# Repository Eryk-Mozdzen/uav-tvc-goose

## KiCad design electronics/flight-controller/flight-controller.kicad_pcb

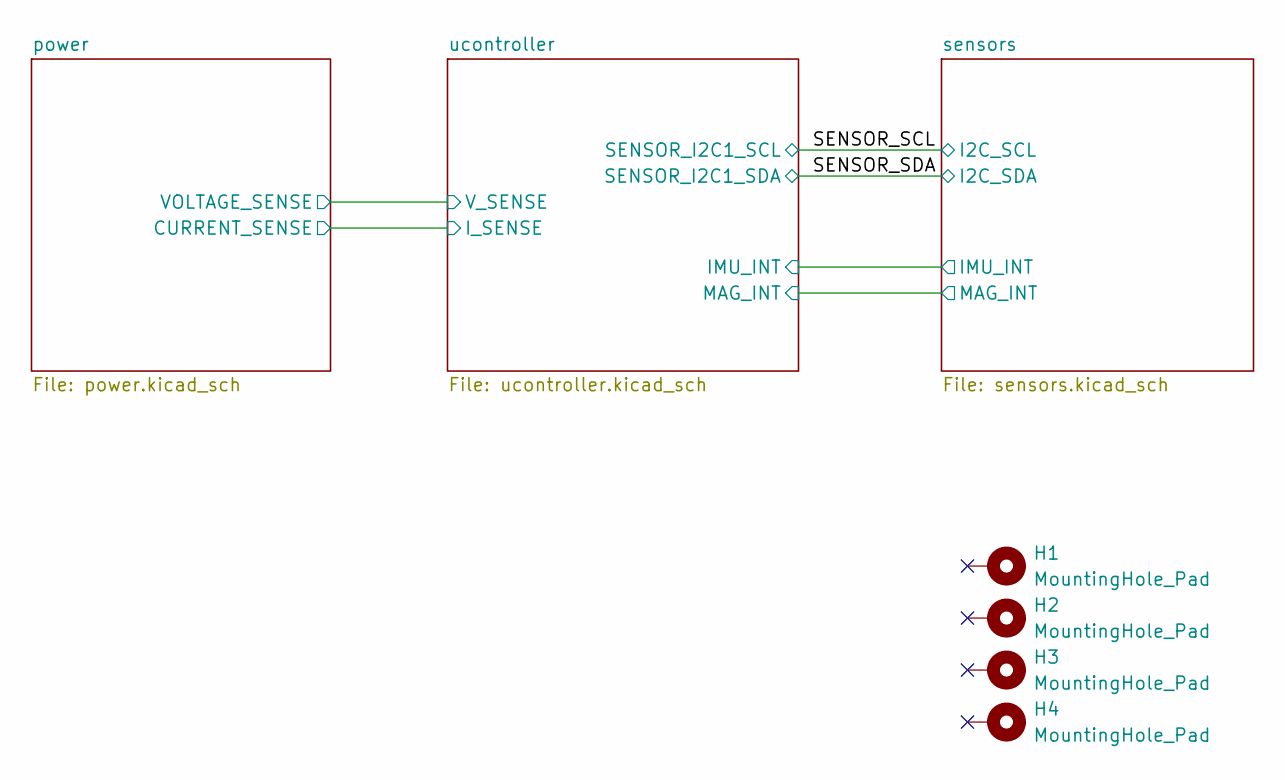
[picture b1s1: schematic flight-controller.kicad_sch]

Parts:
H1, H2, H3, H4: MountingHole_Pad; MountingHole_3.2mm_M3_Pad_Via

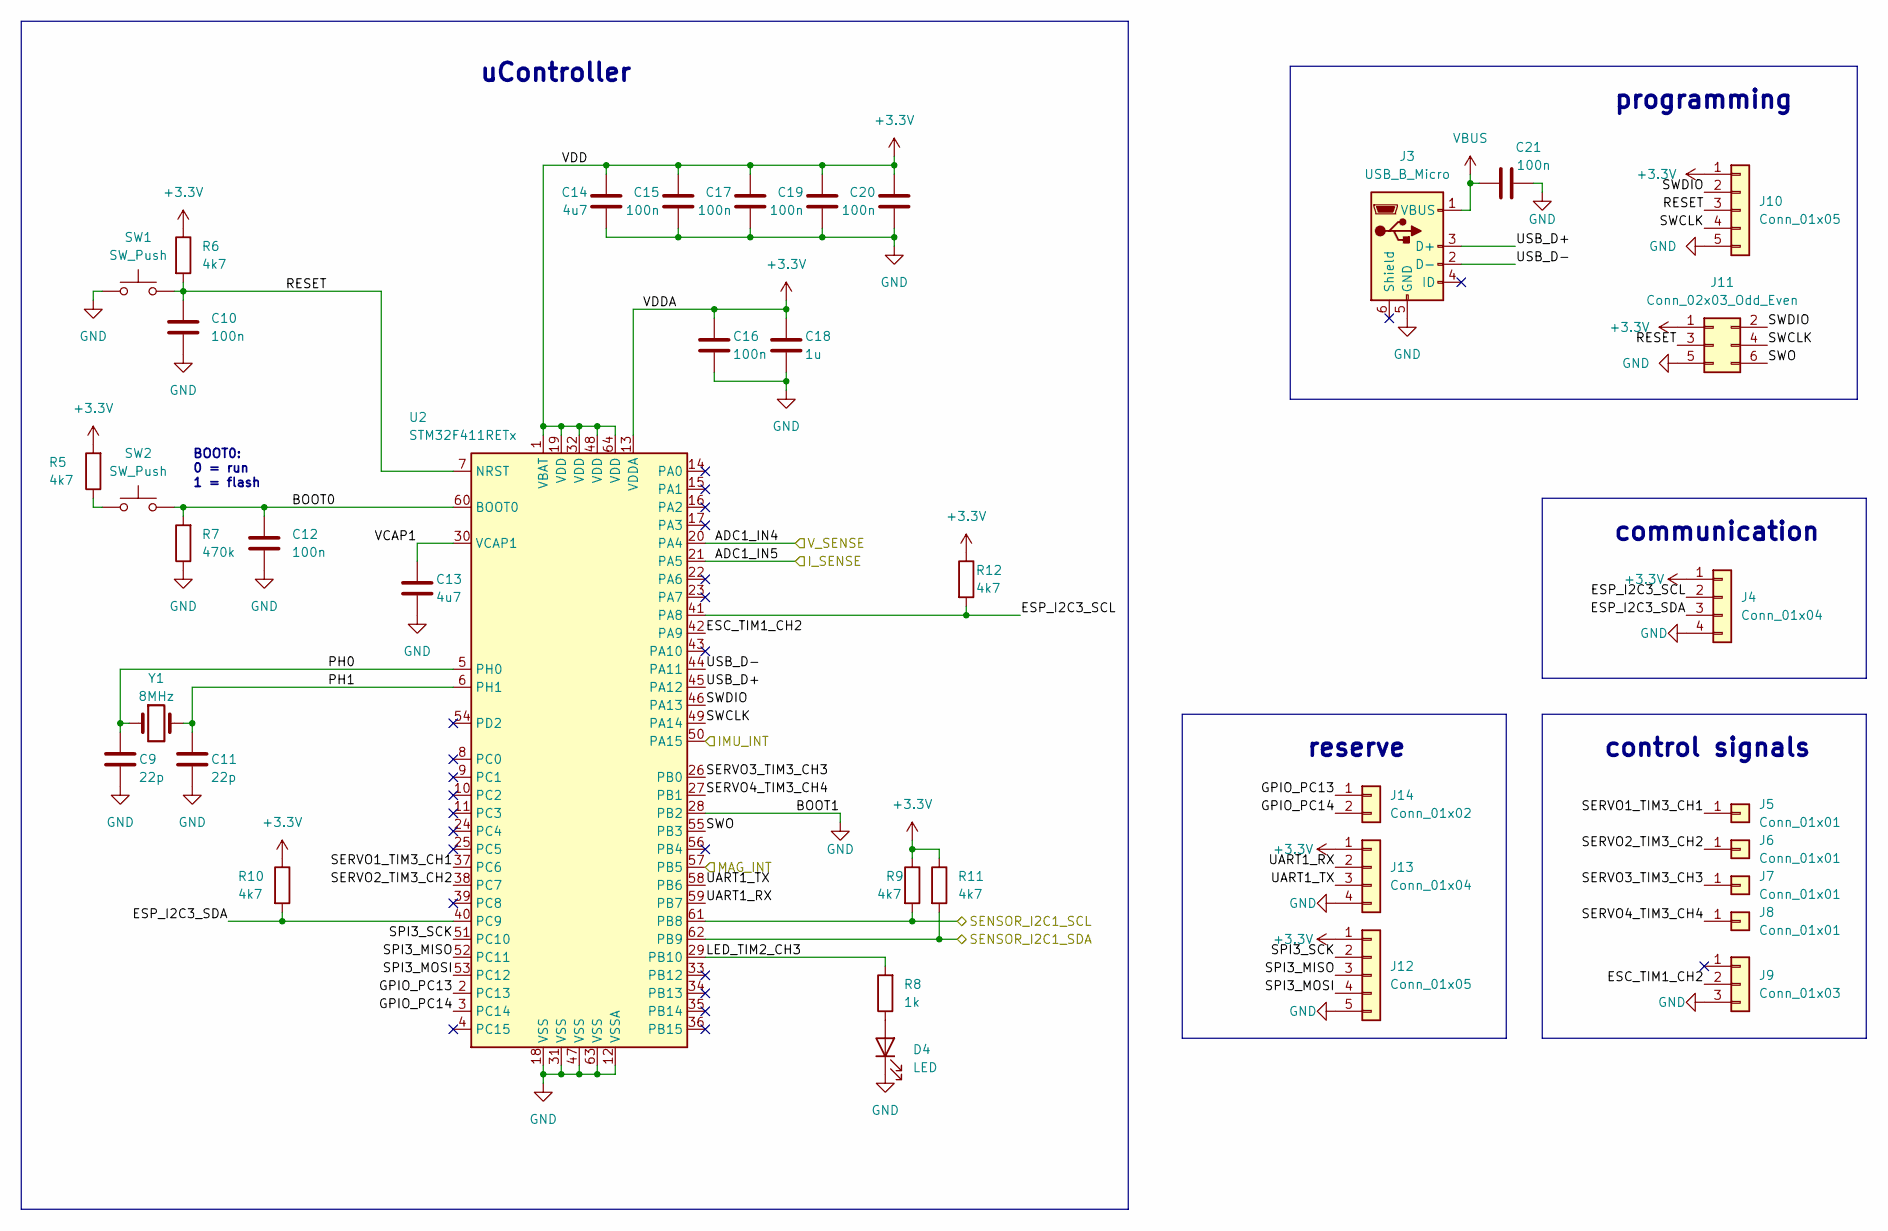
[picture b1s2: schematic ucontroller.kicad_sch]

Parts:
C9, C11: 22p; C_0603_1608Metric
C10, C12, C15, C16, C17, C19, C20, C21: 100n; C_0603_1608Metric
C13, C14: 4u7; C_0603_1608Metric
C18: 1u; C_0603_1608Metric
D4: LED; LED_0603_1608Metric
J3: USB_B_Micro; usb_micro_B_druk_II
J4, J13: Conn_01x04; tht_pin_01x04
J5, J6, J7, J8: Conn_01x01; tht_pin_01x01
J9: Conn_01x03; tht_pin_01x03
J10, J12: Conn_01x05; tht_pin_01x05
J11: Conn_02x03_Odd_Even; Tag-Connect_TC2030-IDC-NL_2x03_P1.27mm_Vertical
J14: Conn_01x02; tht_pin_01x02
R5, R6, R9, R10, R11, R12: 4k7; R_0603_1608Metric
R7: 470k; R_0603_1608Metric
R8: 1k; R_0603_1608Metric
SW1, SW2: SW_Push; SW_Push_1P1T_NO_CK_KMR2
U2: STM32F411RETx; LQFP-64_10x10mm_P0.5mm
Y1: 8MHz; Crystal_SMD_5032-2Pin_5.0x3.2mm

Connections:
+3.3V: C14.1, C15.1, C16.1, C17.1, C18.1, C19.1, C20.1, J4.1, J10.1, J11.1, J12.1, J13.1, R5.2, R6.1, R9.1, R10.1, R11.1, R12.1, U2.1 (VBAT), U2.13 (VDDA), U2.19 (VDD), U2.32 (VDD), U2.48 (VDD), U2.64 (VDD); also elsewhere on the board
/SENSOR_SCL: R9.2, U2.61 (PB8); also elsewhere on the board
/SENSOR_SDA: R11.2, U2.62 (PB9); also elsewhere on the board
/power/I_FILTER: U2.21 (PA5); also elsewhere on the board
/power/V_FILTER: U2.20 (PA4); also elsewhere on the board
/sensors/IMU_INT: U2.50 (PA15); also elsewhere on the board
/sensors/MAG_INT: U2.57 (PB5); also elsewhere on the board
/ucontroller/BOOT0: C12.1, R7.2, SW2.2, U2.60 (BOOT0)
/ucontroller/ESC_TIM1_CH2: J9.2, U2.42 (PA9)
/ucontroller/ESP_I2C3_SCL: J4.2, R12.2, U2.41 (PA8)
/ucontroller/ESP_I2C3_SDA: J4.3, R10.2, U2.40 (PC9)
/ucontroller/GPIO_PC13: J14.1, U2.2 (PC13)
/ucontroller/GPIO_PC14: J14.2, U2.3 (PC14)
/ucontroller/LED_TIM2_CH3: R8.2, U2.29 (PB10)
/ucontroller/PH0: C9.1, U2.5 (PH0), Y1.1
/ucontroller/PH1: C11.1, U2.6 (PH1), Y1.2
/ucontroller/RESET: C10.1, J10.3, J11.3, R6.2, SW1.2, U2.7 (NRST)
/ucontroller/SERVO1_TIM3_CH1: J5.1, U2.37 (PC6)
/ucontroller/SERVO2_TIM3_CH2: J6.1, U2.38 (PC7)
/ucontroller/SERVO3_TIM3_CH3: J7.1, U2.26 (PB0)
/ucontroller/SERVO4_TIM3_CH4: J8.1, U2.27 (PB1)
/ucontroller/SPI3_MISO: J12.3, U2.52 (PC11)
/ucontroller/SPI3_MOSI: J12.4, U2.53 (PC12)
/ucontroller/SPI3_SCK: J12.2, U2.51 (PC10)
/ucontroller/SWCLK: J10.4, J11.4, U2.49 (PA14)
/ucontroller/SWDIO: J10.2, J11.2, U2.46 (PA13)
/ucontroller/SWO: J11.6, U2.55 (PB3)
/ucontroller/UART1_RX: J13.2, U2.59 (PB7)
/ucontroller/UART1_TX: J13.3, U2.58 (PB6)
/ucontroller/USB_D+: J3.3 (D+), U2.45 (PA12)
/ucontroller/USB_D-: J3.2 (D-), U2.44 (PA11)
/ucontroller/VCAP1: C13.1, U2.30 (VCAP1)
GND: C9.2, C10.2, C11.2, C12.2, C13.2, C14.2, C15.2, C16.2, C17.2, C18.2, C19.2, C20.2, C21.2, D4.1 (K), J3.5 (GND), J4.4, J9.3, J10.5, J11.5, J12.5, J13.4, R7.1, SW1.1, U2.12 (VSSA), U2.18 (VSS), U2.28 (PB2), U2.31 (VSS), U2.47 (VSS), U2.63 (VSS); also elsewhere on the board
unnamed: D4.2 (A), R8.1
unnamed: R5.1, SW2.1
VBUS: C21.1, J3.1 (VBUS); also elsewhere on the board

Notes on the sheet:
BOOT0: 0 = run 1 = flash
programming
uController
reserve
communication
control signals

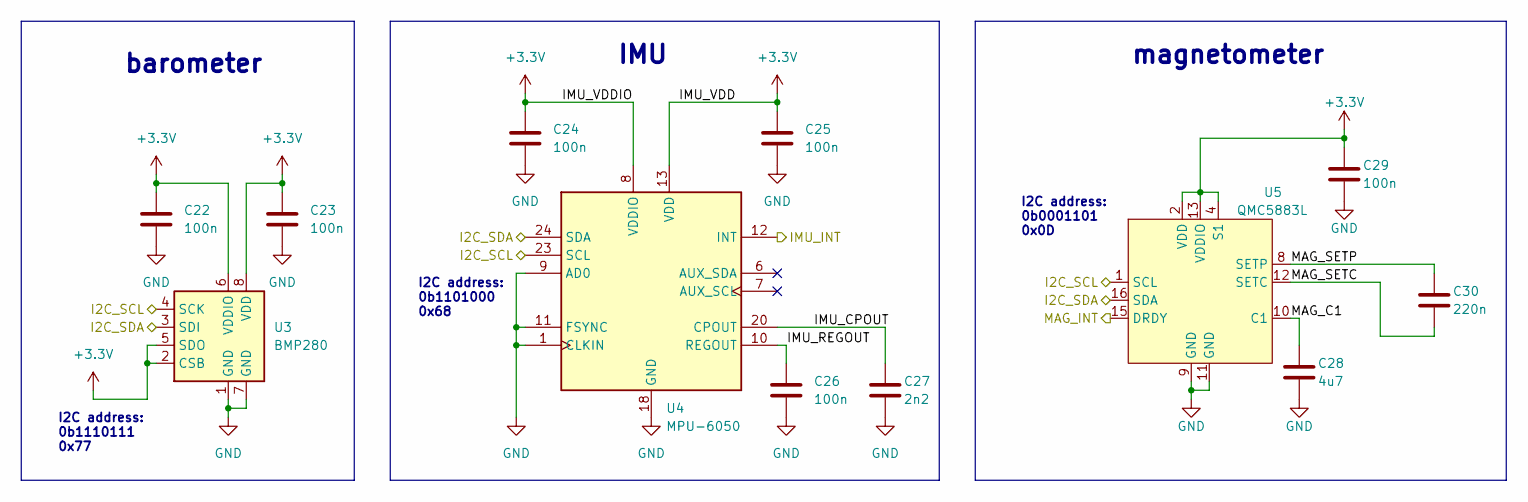
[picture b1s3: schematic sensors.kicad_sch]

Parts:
C22, C23, C24, C25, C26, C29: 100n; C_0603_1608Metric
C27: 2n2; C_0603_1608Metric
C28: 4u7; C_0603_1608Metric
C30: 220n; C_0603_1608Metric
U3: BMP280; bmp280_hand_solder
U4: MPU-6050; mpu6050_hand_solder
U5: QMC5883L; qmc5883l_hand_solder

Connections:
+3.3V: C22.1, C23.1, C24.1, C25.1, C29.1, U3.2 (CSB), U3.5 (SDO), U3.6 (VDDIO), U3.8 (VDD), U4.8 (VDDIO), U4.13 (VDD), U5.2 (VDD), U5.4 (S1), U5.13 (VDDIO); also elsewhere on the board
/SENSOR_SCL: U3.4 (SCK), U4.23 (SCL), U5.1 (SCL); also elsewhere on the board
/SENSOR_SDA: U3.3 (SDI), U4.24 (SDA), U5.16 (SDA); also elsewhere on the board
/sensors/IMU_CPOUT: C27.1, U4.20 (CPOUT)
/sensors/IMU_INT: U4.12 (INT); also elsewhere on the board
/sensors/IMU_REGOUT: C26.1, U4.10 (REGOUT)
/sensors/MAG_C1: C28.1, U5.10 (C1)
/sensors/MAG_INT: U5.15 (DRDY); also elsewhere on the board
/sensors/MAG_SETC: C30.2, U5.12 (SETC)
/sensors/MAG_SETP: C30.1, U5.8 (SETP)
GND: C22.2, C23.2, C24.2, C25.2, C26.2, C27.2, C28.2, C29.2, U3.1 (GND), U3.7 (GND), U4.1 (CLKIN), U4.9 (AD0), U4.11 (FSYNC), U4.18 (GND), U5.9 (GND), U5.11 (GND); also elsewhere on the board

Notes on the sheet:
IMU
I2C address: 0b1101000 0x68
I2C address: 0b0001101 0x0D
magnetometer
I2C address: 0b1110111 0x77
barometer

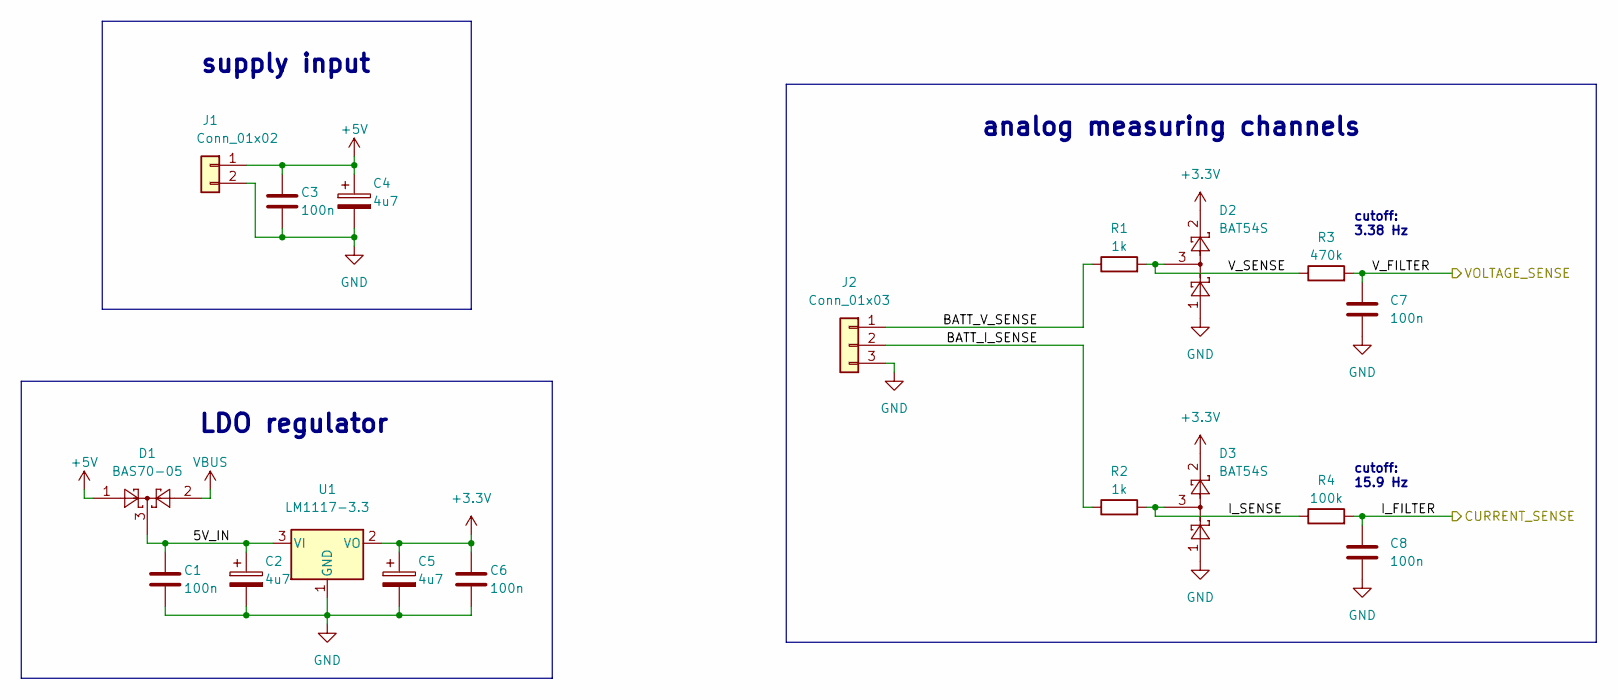
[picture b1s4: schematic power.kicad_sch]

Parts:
C1, C3, C6, C7, C8: 100n; C_0603_1608Metric
C2, C4, C5: 4u7; CP_EIA-3216-18_Kemet-A
D1: BAS70-05; SOT-23
D2, D3: BAT54S; SOT-23
J1: Conn_01x02; tht_pin_01x02
J2: Conn_01x03; tht_pin_01x03
R1, R2: 1k; R_0603_1608Metric
R3: 470k; R_0603_1608Metric
R4: 100k; R_0603_1608Metric
U1: LM1117-3.3; SOT-223-3_TabPin2

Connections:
+3.3V: C5.1, C6.1, D2.2, D3.2, U1.2 (VO); also elsewhere on the board
+5V: C3.1, C4.1, D1.1, J1.1
/power/5V_IN: C1.1, C2.1, D1.3, U1.3 (VI)
/power/BATT_I_SENSE: J2.2, R2.1
/power/BATT_V_SENSE: J2.1, R1.1
/power/I_FILTER: C8.1, R4.2; also elsewhere on the board
/power/I_SENSE: D3.3, R2.2, R4.1
/power/V_FILTER: C7.1, R3.2; also elsewhere on the board
/power/V_SENSE: D2.3, R1.2, R3.1
GND: C1.2, C2.2, C3.2, C4.2, C5.2, C6.2, C7.2, C8.2, D2.1, D3.1, J1.2, J2.3, U1.1 (GND); also elsewhere on the board
VBUS: D1.2; also elsewhere on the board

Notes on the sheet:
supply input
LDO regulator
cutoff: 3.38 Hz
cutoff: 15.9 Hz
analog measuring channels

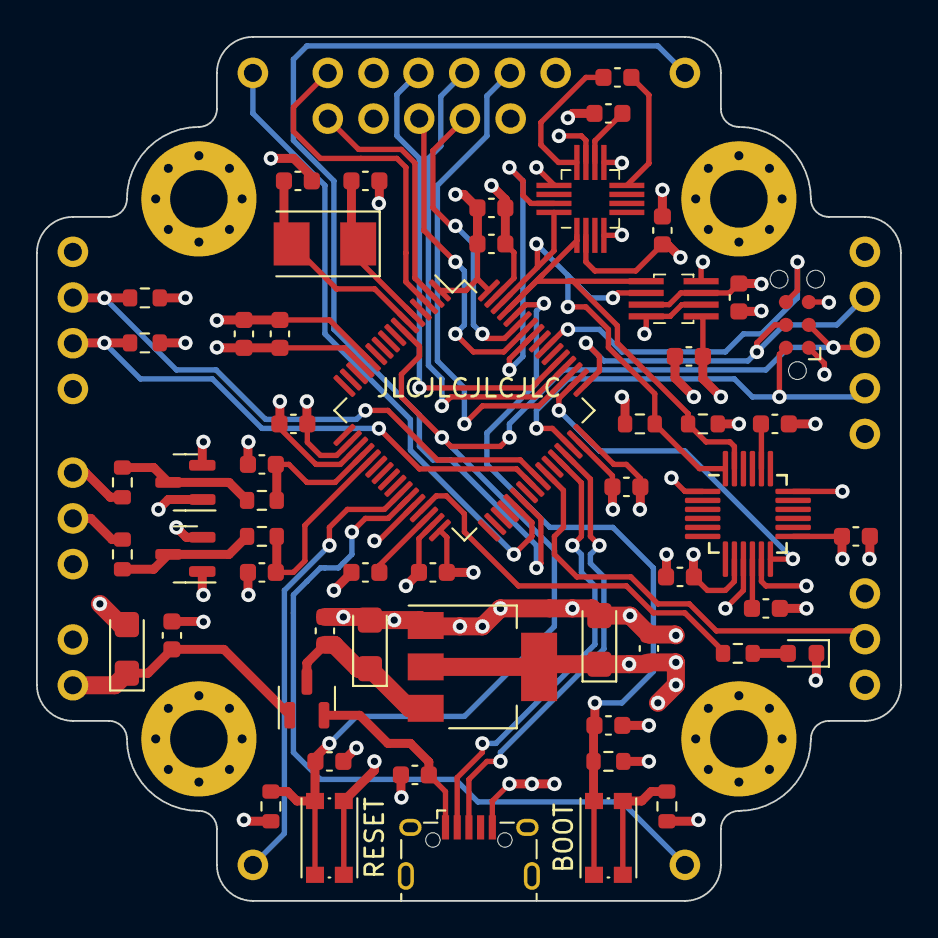
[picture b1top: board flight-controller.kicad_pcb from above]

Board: 4 copper layers, 48.0 x 48.0 mm, 72 parts (0 on the bottom side), 47 nets.

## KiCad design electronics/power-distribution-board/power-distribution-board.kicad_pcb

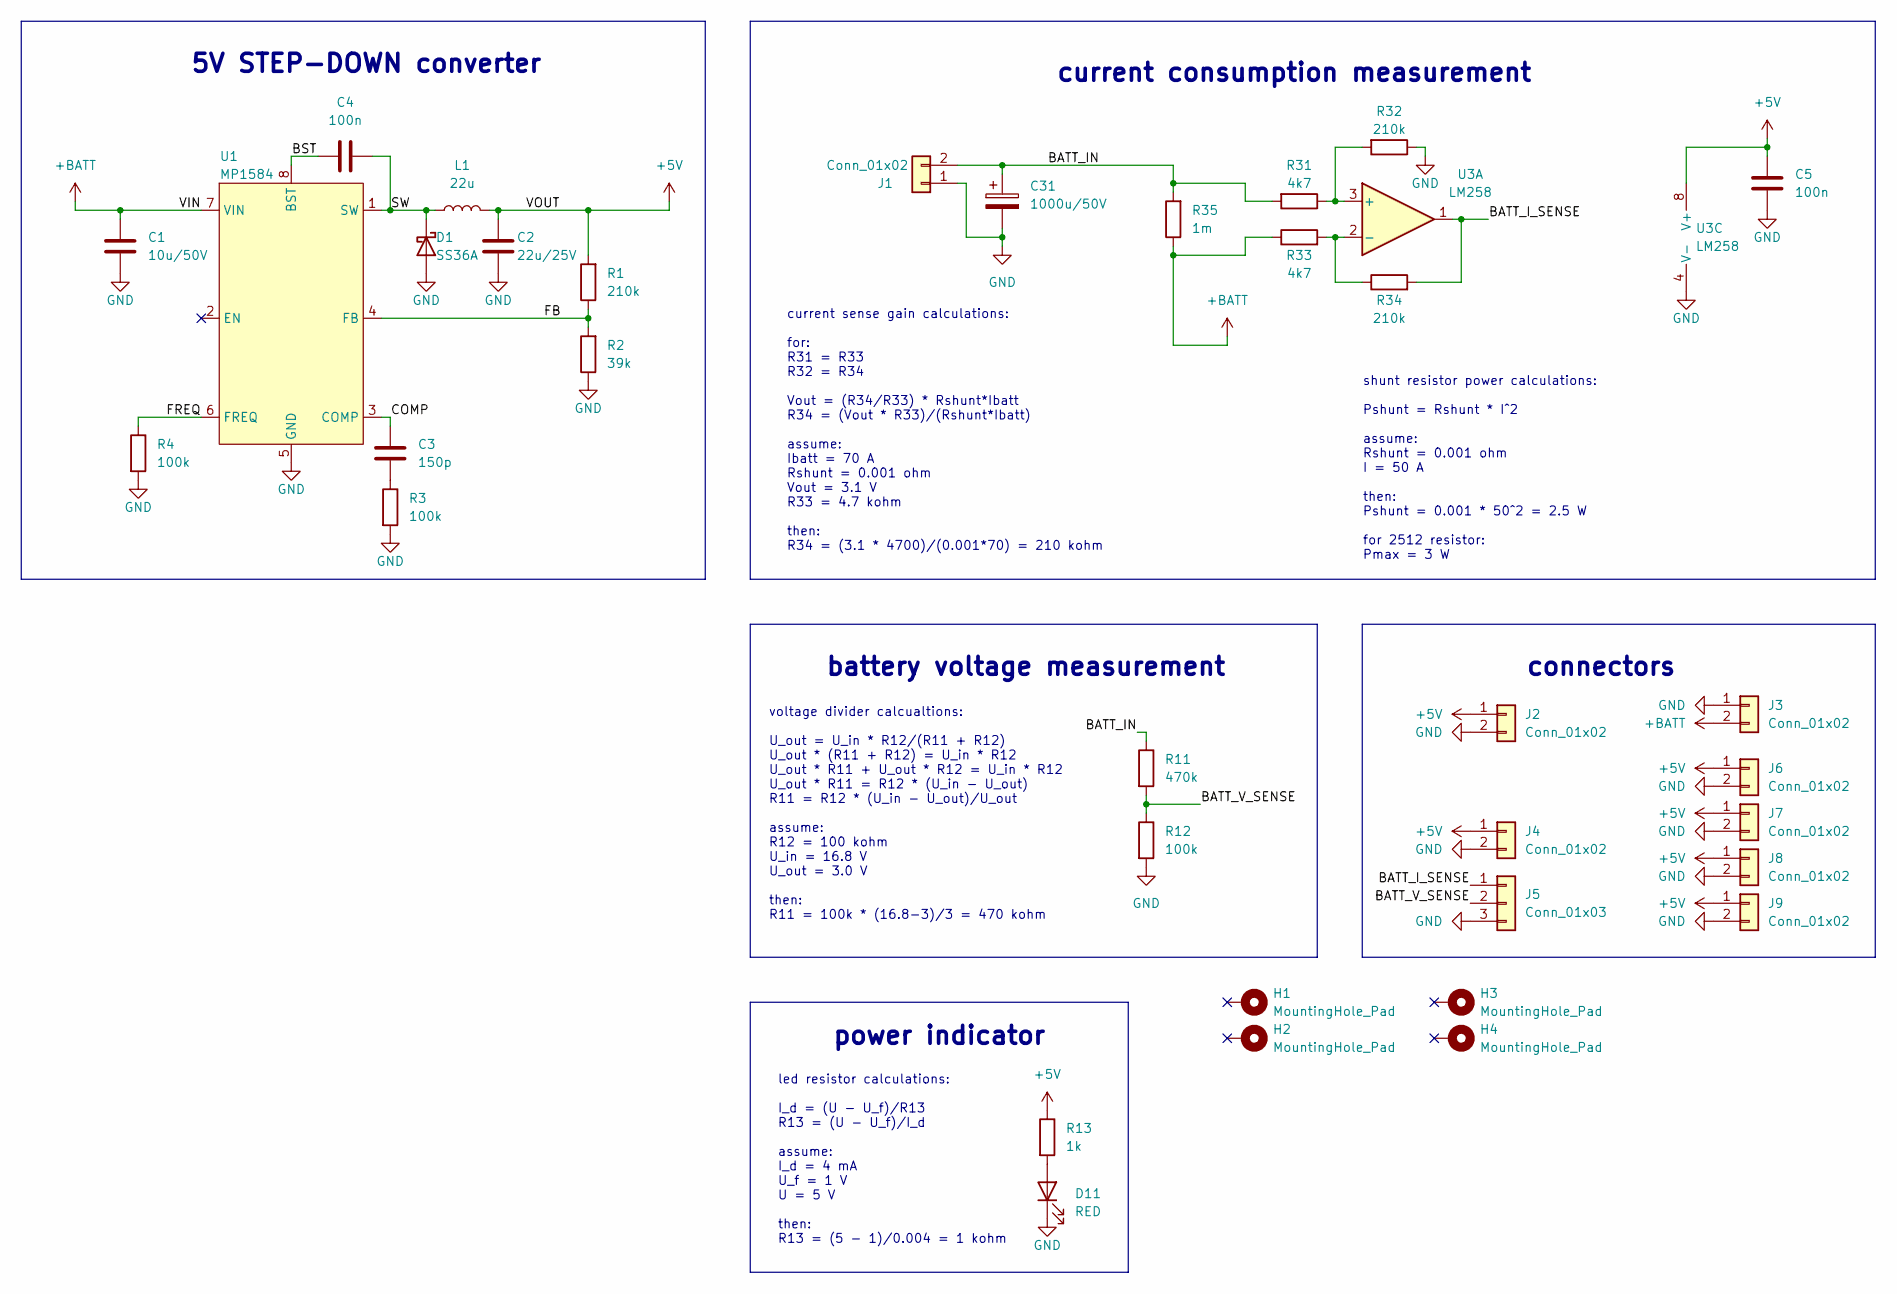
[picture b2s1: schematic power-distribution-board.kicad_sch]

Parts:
C1: 10u/50V; C_1206_3216Metric
C2: 22u/25V; C_1206_3216Metric
C3: 150p; C_0603_1608Metric
C4, C5: 100n; C_0603_1608Metric
C31: 1000u/50V
D1: SS36A; D_SMA
D11: RED; LED_0603_1608Metric
H1, H2, H3, H4: MountingHole_Pad; MountingHole_3.2mm_M3_Pad_Via
J1: Conn_01x02; AMASS_XT60-M_1x02_P7.20mm_Vertical
J2, J4, J6, J7, J8, J9: Conn_01x02; tht_pin_01x02
J3: Conn_01x02
J5: Conn_01x03; tht_pin_01x03
L1: 22u; L_12x12mm_H6mm
R1, R32, R34: 210k; R_0603_1608Metric
R2: 39k; R_0603_1608Metric
R3, R4, R12: 100k; R_0603_1608Metric
R11: 470k; R_0603_1608Metric
R13: 1k; R_0603_1608Metric
R31, R33: 4k7; R_0603_1608Metric
R35: 1m; R_2512_6332Metric
U1: MP1584; SOIC-8-1EP_3.9x4.9mm_P1.27mm_EP2.62x3.51mm_ThermalVias
U3: LM258; SOIC-8_3.9x4.9mm_P1.27mm

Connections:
+5V: C2.2, C5.2, J2.1, J4.1, J6.1, J7.1, J8.1, J9.1, L1.2, R1.2, R13.1, U3.8 (V+)
+BATT: C1.2, J3.2, R33.1, R35.1, U1.7 (VIN)
/BATT_IN: C31.1, J1.2, R11.1, R31.2, R35.2
/BATT_I_SENSE: J5.1, R34.2, U3.1
/BATT_V_SENSE: J5.2, R11.2, R12.1
/BST: C4.1, U1.8 (BST)
/COMP: C3.1, U1.3 (COMP)
/FB: R1.1, R2.2, U1.4 (FB)
/FREQ: R4.1, U1.6 (FREQ)
/SW: C4.2, D1.1 (K), L1.1, U1.1 (SW)
GND: C1.1, C2.1, C5.1, C31.2, D1.2 (A), D11.1 (K), J1.1, J2.2, J3.1, J4.2, J5.3, J6.2, J7.2, J8.2, J9.2, R2.1, R3.2, R4.2, R12.2, R32.1, U1.5 (GND), U3.4 (V-)
unnamed: C3.2, R3.1
unnamed: D11.2 (A), R13.2
unnamed: R31.1, R32.2, U3.3 (+)
unnamed: R33.2, R34.1, U3.2 (-)

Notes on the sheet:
5V STEP-DOWN converter
power indicator
current consumption measurement
led resistor calculations: I_d = (U - U_f)/R13 R13 = (U - U_f)/I_d assume: I_d = 4 mA U_f = 1 V U = 5 V then: R13 = (5 - 1)/0.004 = 1 kohm
current sense gain calculations: for: R31 = R33 R32 = R34 Vout = (R34/R33) * Rshunt*Ibatt R34 = (Vout * R33)/(Rshunt*Ibatt) assume: Ibatt = 70 A Rshunt = 0.001 ohm Vout = 3.1 V R33 = 4.7 kohm then: R34 = (3.1 * 4700)/(0.001*70) = 210 kohm
shunt resistor power calculations: Pshunt = Rshunt * I^2 assume: Rshunt = 0.001 ohm I = 50 A then: Pshunt = 0.001 * 50^2 = 2.5 W for 2512 resistor: Pmax = 3 W
connectors
voltage divider calcualtions: U_out = U_in * R12/(R11 + R12) U_out * (R11 + R12) = U_in * R12 U_out * R11 + U_out * R12 = U_in * R12 U_out * R11 = R12 * (U_in - U_out) R11 = R12 * (U_in - U_out)/U_out assume: R12 = 100 kohm U_in = 16.8 V U_out = 3.0 V then: R11 = 100k * (16.8-3)/3 = 470 kohm
battery voltage measurement

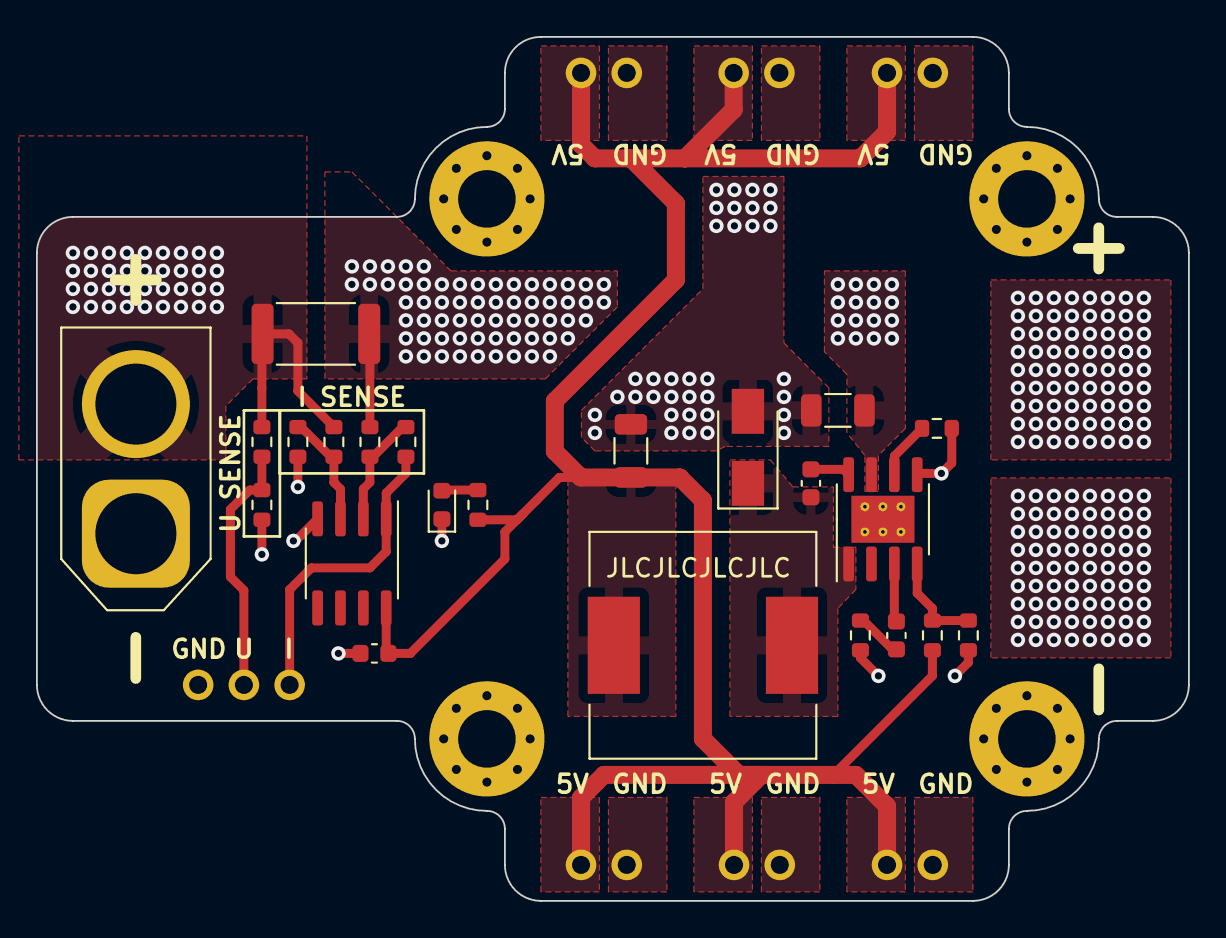
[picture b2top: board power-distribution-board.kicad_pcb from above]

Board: 2 copper layers, 64.0 x 48.0 mm, 34 parts (0 on the bottom side), 15 nets.
